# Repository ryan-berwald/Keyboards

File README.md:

<h1 align="center">Welcome to PotPi MacroPad 👋</h1>
<p>

</p>

> A mechanical macropad featuring a Raspberry Pi Pico microcontroller, an oled screen, 2 rotary encoders, and 2 linear slide potentiometers. The slide potentiometers will emit a value anytime a new value is detected from either of them, and a client running on the host computer will take those values and set the volume for your selected applications. 

## Author

👤 **Ryan Berwald**

* Twitter: [@ryan\_berwald](https://twitter.com/ryan\_berwald)
* Github: [@ryan-berwald](https://github.com/ryan-berwald)
* LinkedIn: [@ryan-berwald](https://linkedin.com/in/ryan-berwald)

## 🤝 Contributing

Contributions, issues and feature requests are welcome!<br />Feel free to check [issues page](https://github.com/ryan-berwald/Keyboards/issues). 

## Show your support

Give a ⭐️ if this project helped you!

***
_This README was generated with ❤️ by [readme-md-generator](https://github.com/kefranabg/readme-md-generator)_

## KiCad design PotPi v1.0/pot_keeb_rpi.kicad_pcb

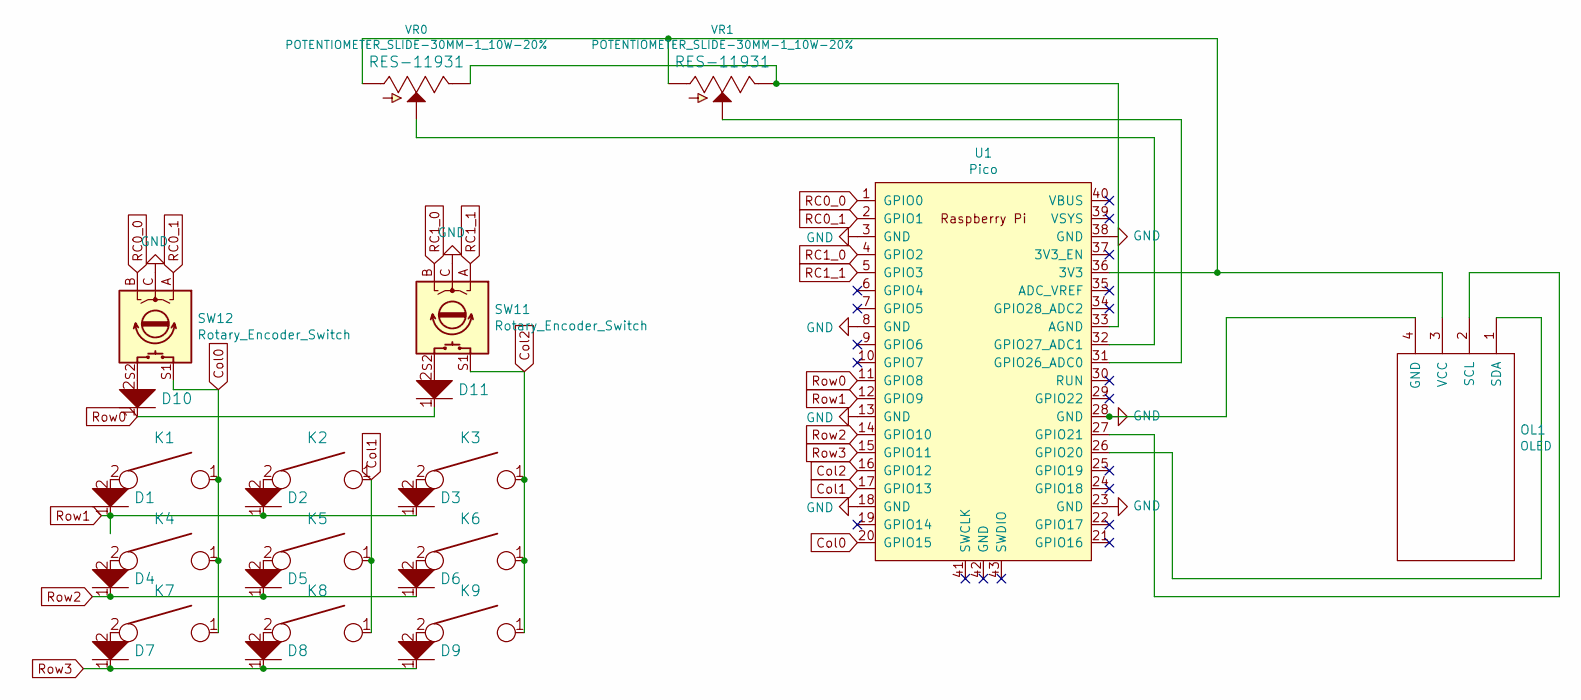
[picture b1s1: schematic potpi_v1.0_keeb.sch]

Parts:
D1, D2, D3, D4, D5, D6, D7, D8, D9, D10, D11: D; D_SOD123_axial
K1, K2, K3, K4, K5, K6, K7, K8, K9: KEYSW; Mx_Alps_100
OL1: OLED
SW11, SW12: Rotary_Encoder_Switch; RotaryEncoder_EC11
U1: Pico; RPi_Pico_SMD_TH
VR0, VR1: POTENTIOMETER_SLIDE-30MM-1_10W-20%; SLIDER-MEDIUM

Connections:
Col0: K1.1, K4.1, K7.1, SW12.S1, U1.20 (GPIO15)
Col1: K2.1, K5.1, K8.1, U1.17 (GPIO13)
Col2: K3.1, K6.1, K9.1, SW11.S1, U1.16 (GPIO12)
GND: OL1.4 (GND), SW11.C, SW12.C, U1.3 (GND), U1.8 (GND), U1.13 (GND), U1.18 (GND), U1.23 (GND), U1.28 (GND), U1.38 (GND)
unnamed: D1.2, K1.2
unnamed: D2.2, K2.2
unnamed: D3.2, K3.2
unnamed: D4.2, K4.2
unnamed: D5.2, K5.2
unnamed: D6.2, K6.2
unnamed: D7.2, K7.2
unnamed: D8.2, K8.2
unnamed: D9.2, K9.2
unnamed: D10.2, SW12.S2
unnamed: D11.2, SW11.S2
unnamed: OL1.1 (SDA), U1.26 (GPIO20)
unnamed: OL1.2 (SCL), U1.27 (GPIO21)
unnamed: OL1.3 (VCC), U1.36 (3V3), VR0.BOTT (A), VR1.BOTT (A)
unnamed: U1.31 (GPIO26_ADC0), VR1.WIPE (S)
unnamed: U1.32 (GPIO27_ADC1), VR0.WIPE (S)
unnamed: U1.33 (AGND), VR0.TOP (E), VR1.TOP (E)
RC0_0: SW12.B, U1.1 (GPIO0)
RC0_1: SW12.A, U1.2 (GPIO1)
RC1_0: SW11.B, U1.4 (GPIO2)
RC1_1: SW11.A, U1.5 (GPIO3)
Row0: D10.1, D11.1, U1.11 (GPIO8)
Row1: D1.1, D2.1, D3.1, U1.12 (GPIO9)
Row2: D4.1, D5.1, D6.1, U1.14 (GPIO10)
Row3: D7.1, D8.1, D9.1, U1.15 (GPIO11)

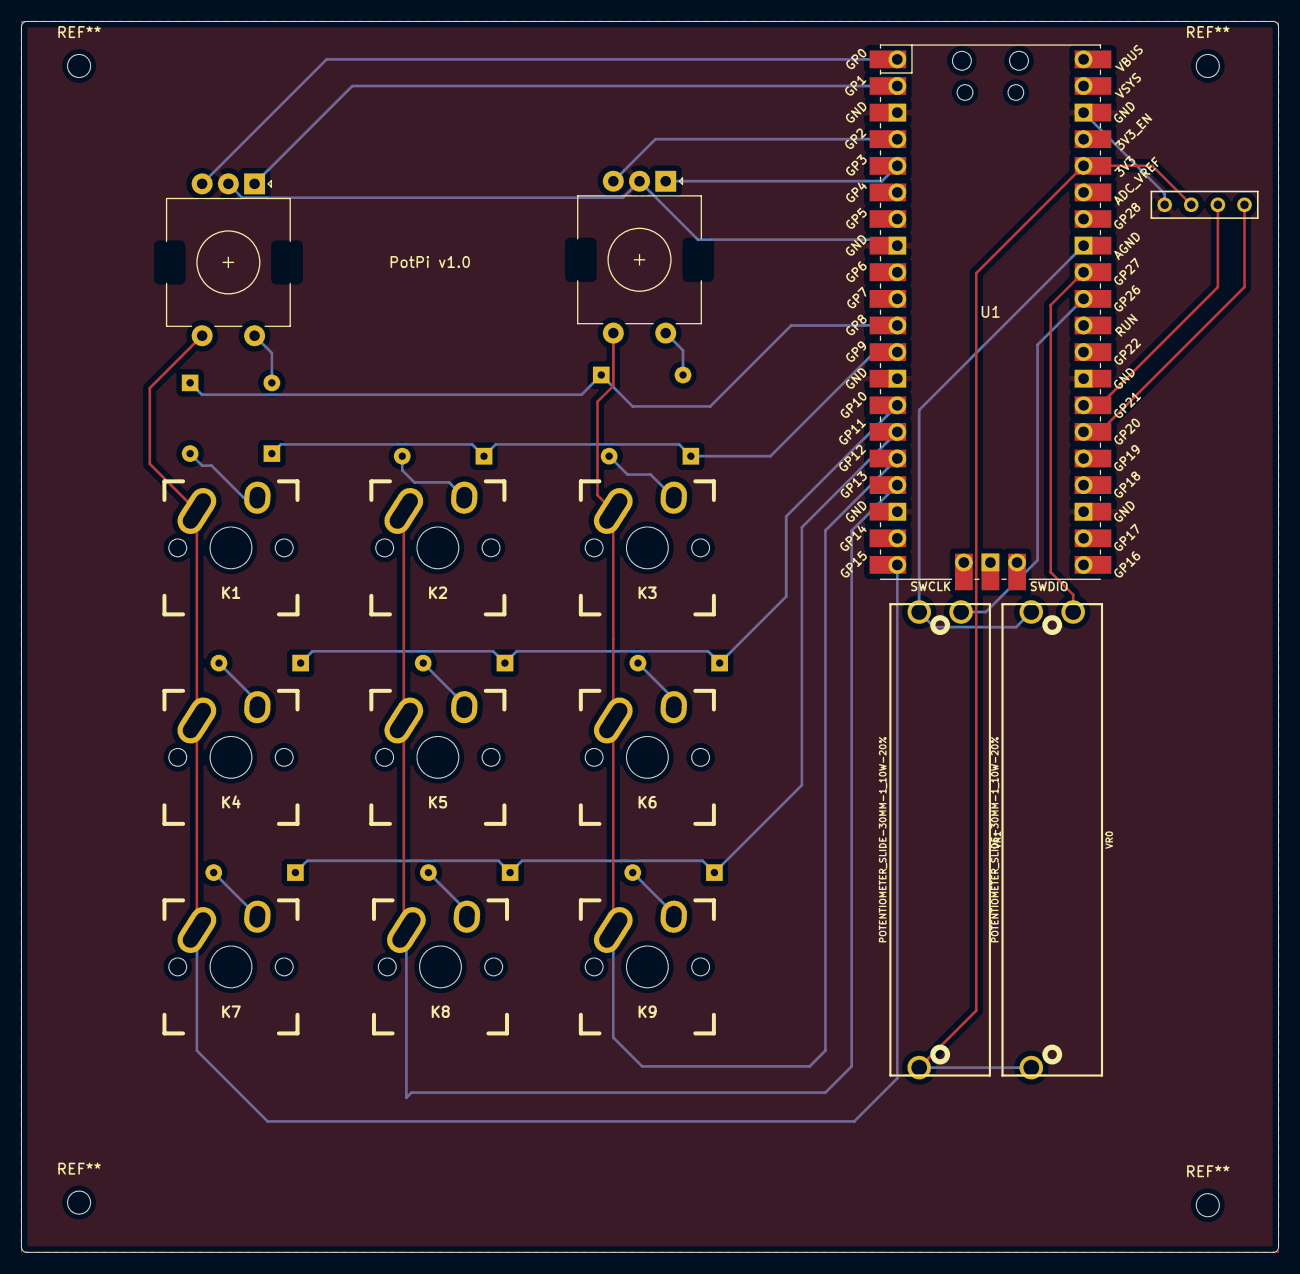
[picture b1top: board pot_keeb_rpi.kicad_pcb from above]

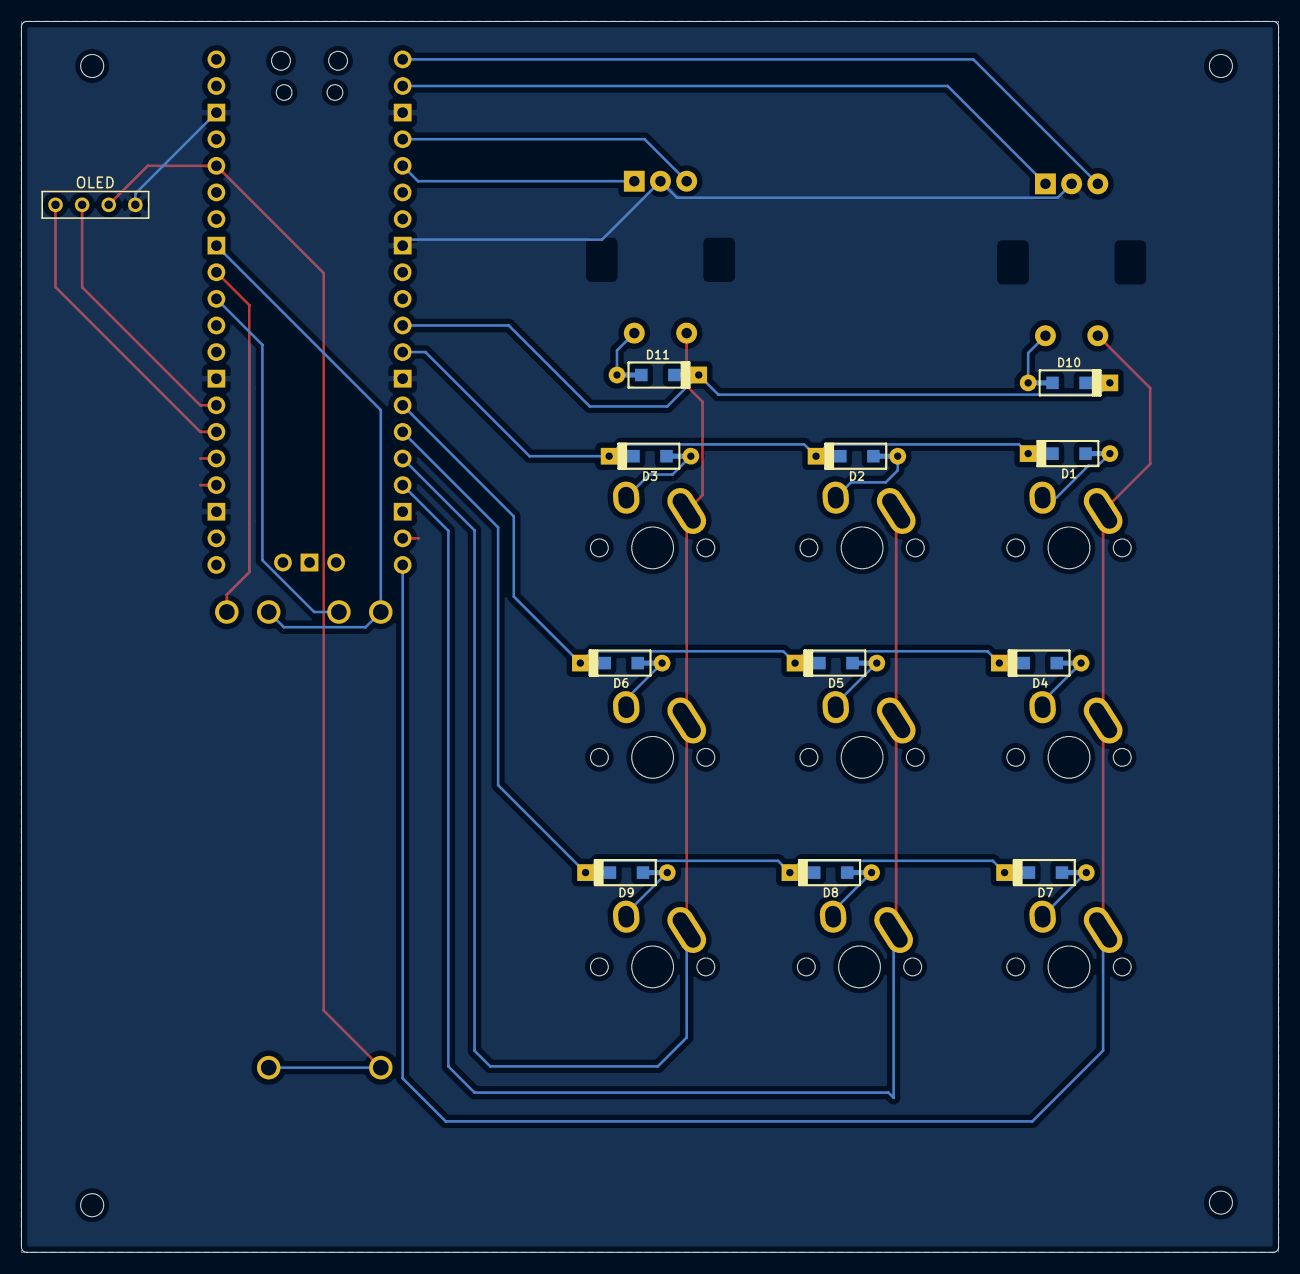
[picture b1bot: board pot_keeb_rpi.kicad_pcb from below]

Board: 2 copper layers, 120.0 x 117.5 mm, 26 parts (12 on the bottom side), 29 nets.

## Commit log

2021-05-18 pushing for v1 update and confirmation of full functionality of all components
2021-05-27 Added case files for PotPi
2021-05-28 Adding firmware
2021-06-06 Updated firmware files for PotPi to include sliders and oled
2021-06-08 Added readme
